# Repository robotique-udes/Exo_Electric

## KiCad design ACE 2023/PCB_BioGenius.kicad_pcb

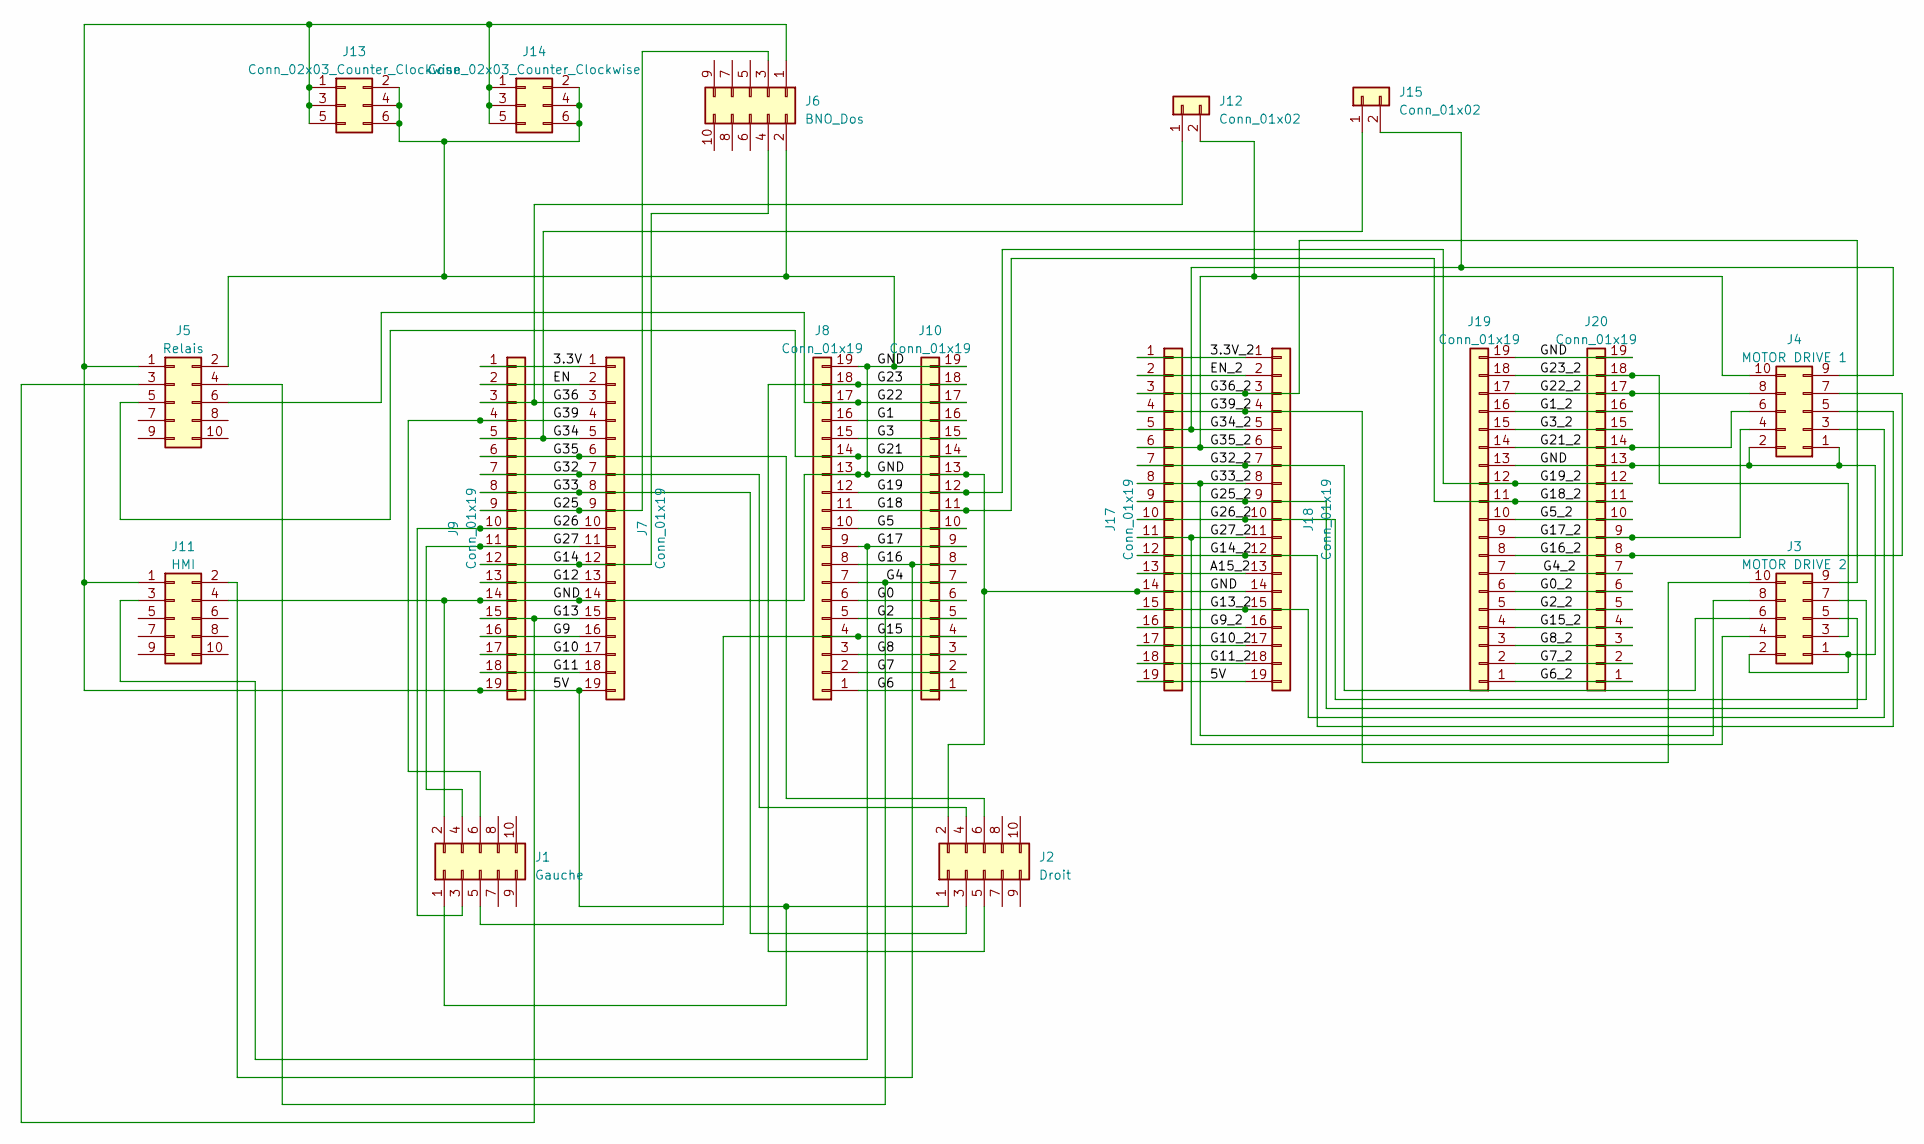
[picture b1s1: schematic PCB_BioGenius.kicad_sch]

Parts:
J1: Gauche; IDC-Header_2x05_P2.54mm_Vertical
J2: Droit; IDC-Header_2x05_P2.54mm_Vertical
J3: MOTOR DRIVE 2; IDC-Header_2x05_P2.54mm_Vertical
J4: MOTOR DRIVE 1; IDC-Header_2x05_P2.54mm_Vertical
J5: Relais; IDC-Header_2x05_P2.54mm_Vertical
J6: BNO_Dos; IDC-Header_2x05_P2.54mm_Vertical
J7, J8, J9, J10, J17, J18, J19, J20: Conn_01x19; PinSocket_1x19_P2.54mm_Vertical
J11: HMI; IDC-Header_2x05_P2.54mm_Vertical
J12, J15: Conn_01x02; PinHeader_1x02_P2.54mm_Vertical
J13, J14: Conn_02x03_Counter_Clockwise; PinSocket_2x03_P2.54mm_Vertical

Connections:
/3.3V: J7.1, J9.1
/3.3V_2: J17.1, J18.1
/A15_2: J17.13, J18.13
/EN: J7.2, J9.2
/EN_2: J17.2, J18.2
/G0: J8.6, J10.6
/G0_2: J19.6, J20.6
/G1: J8.16, J10.16
/G1_2: J19.16, J20.16
/G2: J8.5, J10.5
/G2_2: J19.5, J20.5
/G3: J8.15, J10.15
/G3_2: J19.15, J20.15
/G4: J5.4, J8.7, J10.7
/G4_2: J19.7, J20.7
/G5: J8.10, J10.10
/G5_2: J19.10, J20.10
/G6: J8.1, J10.1
/G6_2: J19.1, J20.1
/G7: J8.2, J10.2
/G7_2: J19.2, J20.2
/G8: J8.3, J10.3
/G8_2: J19.3, J20.3
/G9: J7.16, J9.16
/G9_2: J17.16, J18.16
/G10: J7.17, J9.17
/G10_2: J17.17, J18.17
/G11: J7.18, J9.18
/G11_2: J17.18, J18.18
/G12: J7.13, J9.13
/G13: J5.3, J7.15, J9.15
/G13_2: J4.3, J17.15, J18.15
/G14: J6.4, J7.12, J9.12
/G14_2: J4.5, J17.12, J18.12
/G15: J1.5, J8.4, J10.4
/G15_2: J19.4, J20.4
/G16: J8.8, J10.8, J11.2
/G16_2: J4.7, J19.8, J20.8
/G17: J8.9, J10.9, J11.3
/G17_2: J4.4, J19.9, J20.9
/G18: J8.11, J10.11, J19.11, J20.11
/G19: J8.12, J10.12, J19.12, J20.12
/G21: J5.5, J8.14, J10.14
/G21_2: J4.6, J19.14, J20.14
/G22: J5.6, J8.17, J10.17
/G22_2: J4.8, J19.17, J20.17
/G23: J2.5, J8.18, J10.18
/G23_2: J3.3, J19.18, J20.18
/G25: J6.3, J7.9, J9.9
/G25_2: J3.5, J17.9, J18.9
/G26: J1.3, J7.10, J9.10
/G26_2: J3.7, J17.10, J18.10
/G27: J1.4, J7.11, J9.11
/G27_2: J3.4, J17.11, J18.11
/G32: J2.4, J7.7, J9.7
/G32_2: J3.6, J17.7, J18.7
/G33: J2.3, J7.8, J9.8
/G33_2: J3.8, J17.8, J18.8
/G34: J7.5, J9.5, J15.1
/G34_2: J4.9, J15.2, J17.5, J18.5
/G35: J2.6, J7.6, J9.6
/G36_2: J3.9, J17.3, J18.3
/G39: J1.6, J7.4, J9.4
/G39_2: J3.10, J17.4, J18.4

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
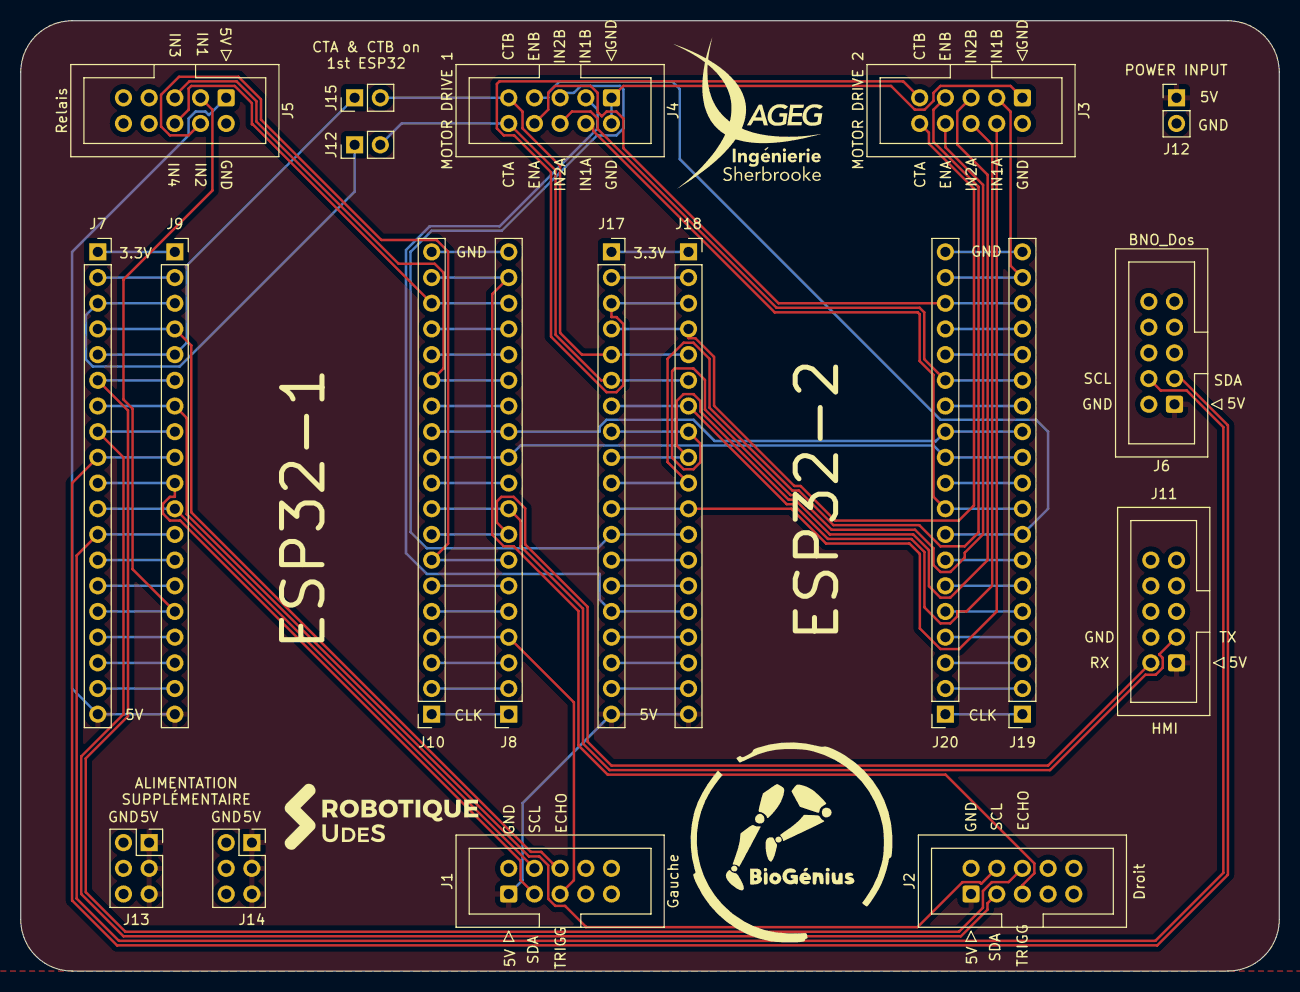
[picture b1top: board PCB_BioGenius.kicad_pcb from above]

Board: 2 copper layers, 124.5 x 94.0 mm, 20 parts (0 on the bottom side), 68 nets.

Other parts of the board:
J12#2: Conn_01x02; PinHeader_1x02_P2.54mm_Vertical

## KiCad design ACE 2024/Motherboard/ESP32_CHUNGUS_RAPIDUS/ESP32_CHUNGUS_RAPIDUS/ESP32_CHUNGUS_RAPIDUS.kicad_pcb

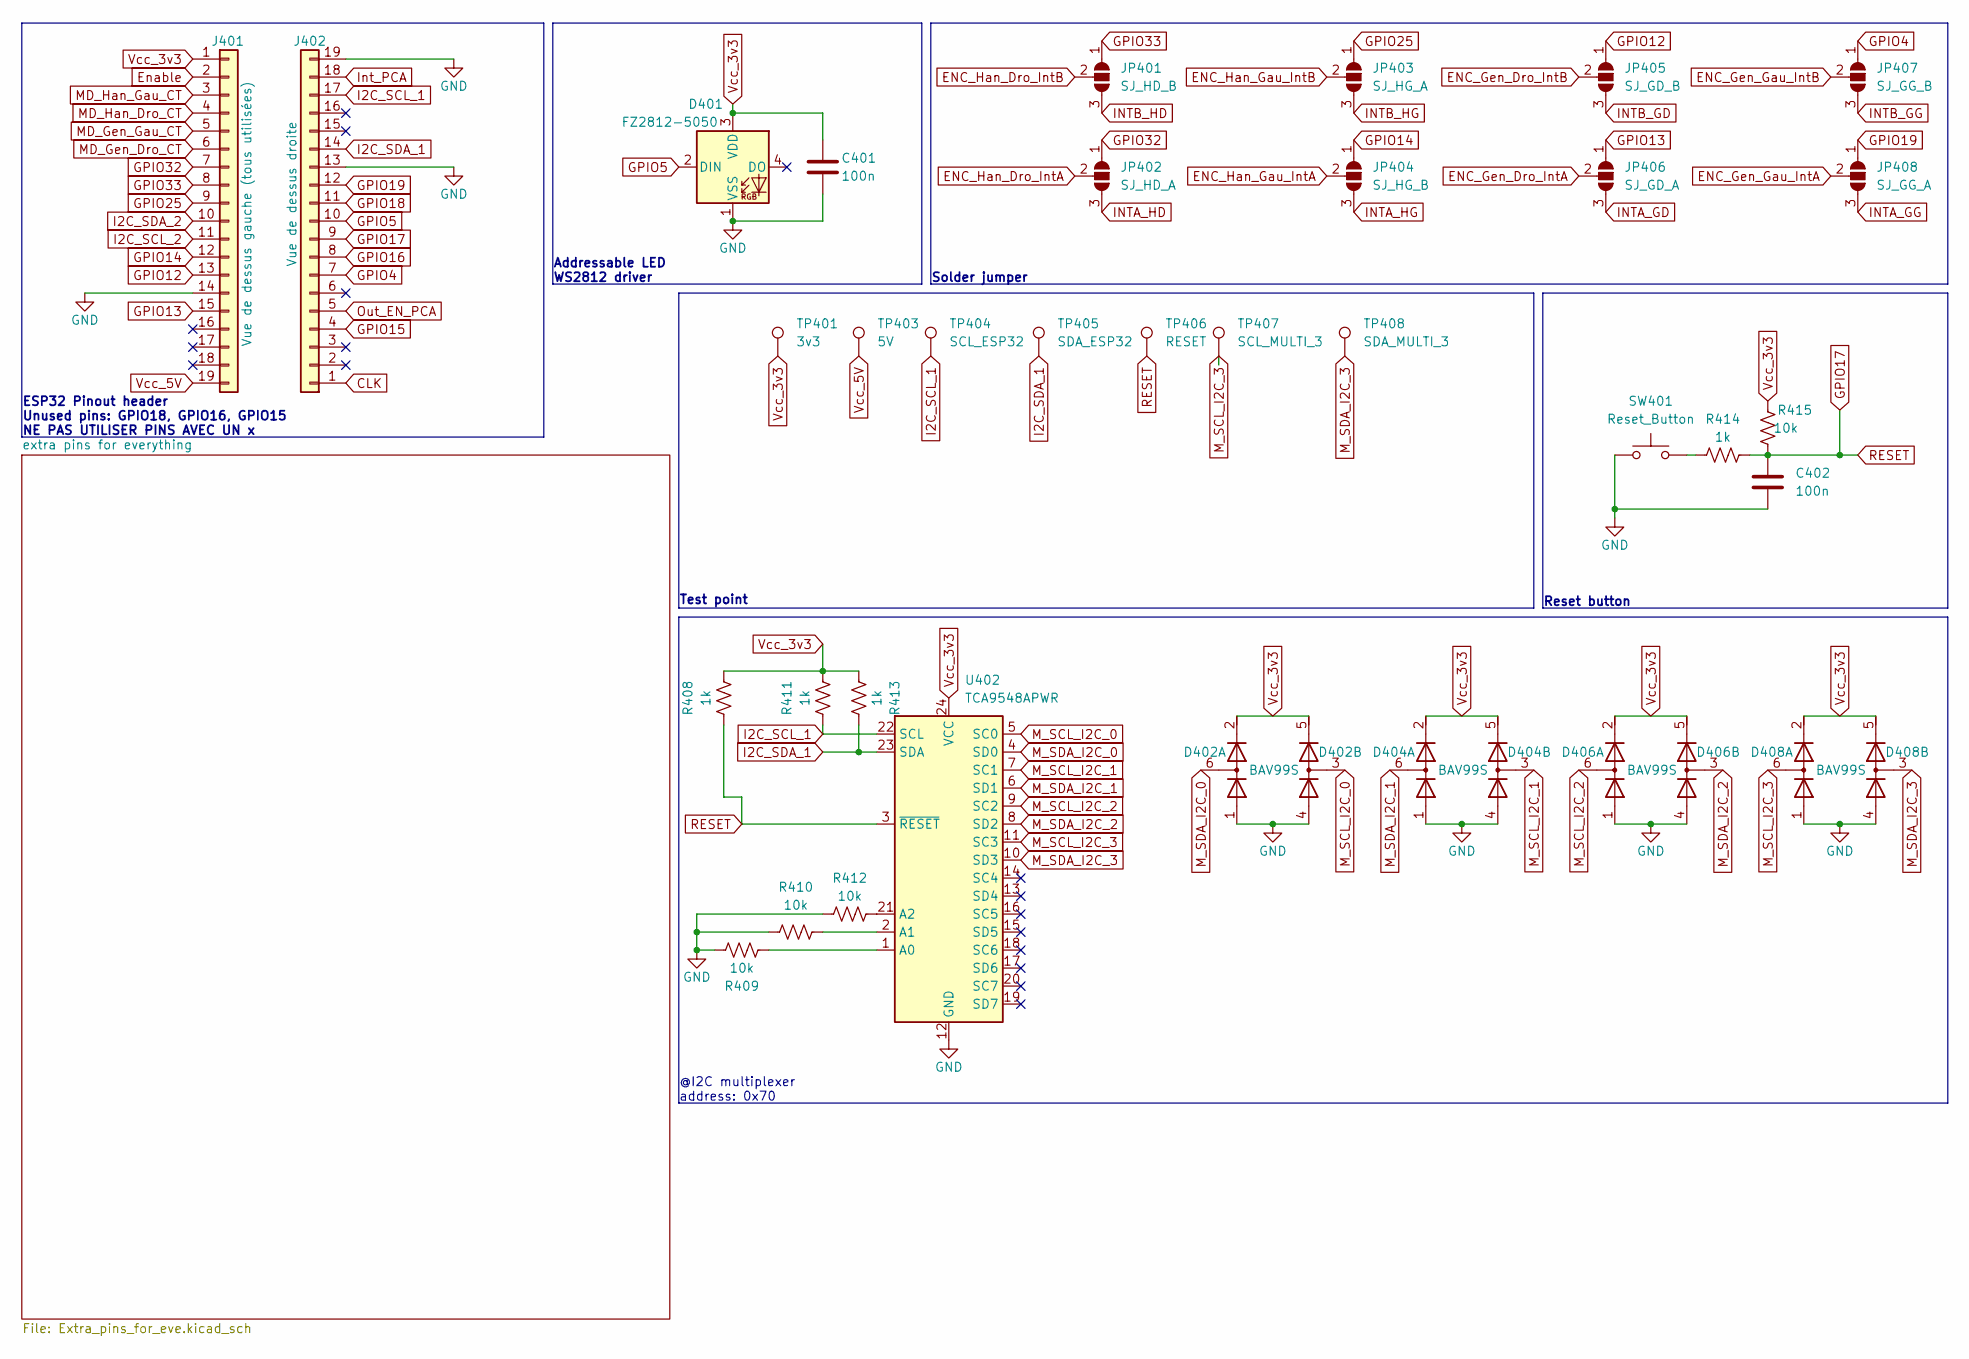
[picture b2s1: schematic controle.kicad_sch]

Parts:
C401, C402: 100n; C_0805_2012Metric
D401: FZ2812-5050; LED_Inolux_IN-PI554FCH_PLCC4_5.0x5.0mm_P3.2mm
D402, D404, D406, D408: BAV99S; SOT-363_SC-70-6
J401: Vue de dessus gauche (tous utilisées); PinSocket_1x19_P2.54mm_Vertical
J402: Vue de dessus droite; PinSocket_1x19_P2.54mm_Vertical
JP401: SJ_HD_B; SolderJumper-3_P2.0mm_Open_TrianglePad1.0x1.5mm_NumberLabels
JP402: SJ_HD_A; SolderJumper-3_P2.0mm_Open_TrianglePad1.0x1.5mm_NumberLabels
JP403: SJ_HG_A; SolderJumper-3_P2.0mm_Open_TrianglePad1.0x1.5mm_NumberLabels
JP404: SJ_HG_B; SolderJumper-3_P2.0mm_Open_TrianglePad1.0x1.5mm_NumberLabels
JP405: SJ_GD_B; SolderJumper-3_P2.0mm_Open_TrianglePad1.0x1.5mm_NumberLabels
JP406: SJ_GD_A; SolderJumper-3_P2.0mm_Open_TrianglePad1.0x1.5mm_NumberLabels
JP407: SJ_GG_B; SolderJumper-3_P2.0mm_Open_TrianglePad1.0x1.5mm_NumberLabels
JP408: SJ_GG_A; SolderJumper-3_P2.0mm_Open_TrianglePad1.0x1.5mm_NumberLabels
R408, R411, R413, R414: 1k; R_0805_2012Metric
R409, R410, R412, R415: 10k; R_0805_2012Metric
SW401: Reset_Button; SW_SPST_PTS645
TP401: 3v3; TestPoint_THTPad_2.5x2.5mm_Drill1.2mm
TP403: 5V; TestPoint_THTPad_2.5x2.5mm_Drill1.2mm
TP404: SCL_ESP32; TestPoint_THTPad_2.5x2.5mm_Drill1.2mm
TP405: SDA_ESP32; TestPoint_THTPad_2.5x2.5mm_Drill1.2mm
TP406: RESET; TestPoint_THTPad_2.5x2.5mm_Drill1.2mm
TP407: SCL_MULTI_3; TestPoint_THTPad_2.5x2.5mm_Drill1.2mm
TP408: SDA_MULTI_3; TestPoint_THTPad_2.5x2.5mm_Drill1.2mm
U402: TCA9548APWR; TSSOP-24_4.4x7.8mm_P0.65mm

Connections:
CLK: J402.1
ENC_Gen_Dro_IntA: JP406.2 (C); also elsewhere on the board
ENC_Gen_Dro_IntB: JP405.2 (C); also elsewhere on the board
ENC_Gen_Gau_IntA: JP408.2 (C); also elsewhere on the board
ENC_Gen_Gau_IntB: JP407.2 (C); also elsewhere on the board
ENC_Han_Dro_IntA: JP402.2 (C); also elsewhere on the board
ENC_Han_Dro_IntB: JP401.2 (C); also elsewhere on the board
ENC_Han_Gau_IntA: JP404.2 (C); also elsewhere on the board
ENC_Han_Gau_IntB: JP403.2 (C); also elsewhere on the board
Enable: J401.2
GND: C401.2, C402.2, D401.1 (VSS), D402.1 (A1), D402.4 (A3), D404.1 (A1), D404.4 (A3), D406.1 (A1), D406.4 (A3), D408.1 (A1), D408.4 (A3), J401.14, J402.13, J402.19, R409.1, R410.2, R412.2, SW401.1, U402.12 (GND); also elsewhere on the board
GPIO4: J402.7, JP407.1 (A)
GPIO5: D401.2 (DIN), J402.10
GPIO12: J401.13, JP405.1 (A)
GPIO13: J401.15, JP406.1 (A)
GPIO14: J401.12, JP404.1 (A)
GPIO15: J402.4
GPIO16: J402.8
GPIO17: C402.1, J402.9, R408.2, R414.1, R415.2, TP406.1, U402.3 (~RESET); also elsewhere on the board
GPIO18: J402.11
GPIO19: J402.12, JP408.1 (A)
GPIO25: J401.9, JP403.1 (A)
GPIO32: J401.7, JP402.1 (A)
GPIO33: J401.8, JP401.1 (A)
I2C_SCL_1: J402.17, R411.2, TP404.1, U402.22 (SCL); also elsewhere on the board
I2C_SCL_2: J401.11
I2C_SDA_1: J402.14, R413.1, TP405.1, U402.23 (SDA); also elsewhere on the board
I2C_SDA_2: J401.10
INTA_GD: JP406.3 (B); also elsewhere on the board
INTA_GG: JP408.3 (B); also elsewhere on the board
INTA_HD: JP402.3 (B); also elsewhere on the board
INTA_HG: JP404.3 (B); also elsewhere on the board
INTB_GD: JP405.3 (B); also elsewhere on the board
INTB_GG: JP407.3 (B); also elsewhere on the board
INTB_HD: JP401.3 (B); also elsewhere on the board
INTB_HG: JP403.3 (B); also elsewhere on the board
Int_PCA: J402.18; also elsewhere on the board
MD_Gen_Dro_CT: J401.6; also elsewhere on the board
MD_Gen_Gau_CT: J401.5; also elsewhere on the board
MD_Han_Dro_CT: J401.4; also elsewhere on the board
MD_Han_Gau_CT: J401.3; also elsewhere on the board
M_SCL_I2C_0: D402.3 (K1A2), U402.5 (SC0); also elsewhere on the board
M_SCL_I2C_1: D404.3 (K1A2), U402.7 (SC1); also elsewhere on the board
M_SCL_I2C_2: D406.6 (K3A4), U402.9 (SC2); also elsewhere on the board
M_SCL_I2C_3: D408.6 (K3A4), TP407.1, U402.11 (SC3)
M_SDA_I2C_0: D402.6 (K3A4), U402.4 (SD0); also elsewhere on the board
M_SDA_I2C_1: D404.6 (K3A4), U402.6 (SD1); also elsewhere on the board
M_SDA_I2C_2: D406.3 (K1A2), U402.8 (SD2); also elsewhere on the board
M_SDA_I2C_3: D408.3 (K1A2), TP408.1, U402.10 (SD3)
unnamed: R414.2, SW401.2
unnamed: R409.2, U402.1 (A0)
unnamed: R410.1, U402.2 (A1)
unnamed: R412.1, U402.21 (A2)
Out_EN_PCA: J402.5; also elsewhere on the board
Vcc_3v3: C401.1, D401.3 (VDD), D402.2 (K2), D402.5 (K4), D404.2 (K2), D404.5 (K4), D406.2 (K2), D406.5 (K4), D408.2 (K2), D408.5 (K4), J401.1, R408.1, R411.1, R413.2, R415.1, TP401.1, U402.24 (VCC); also elsewhere on the board
Vcc_5V: J401.19, TP403.1; also elsewhere on the board

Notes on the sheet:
Reset button
@I2C multiplexer address: 0x70
ESP32 Pinout header Unused pins: GPIO18, GPIO16, GPIO15 NE PAS UTILISER PINS AVEC UN x
Solder jumper
Addressable LED WS2812 driver
Test point

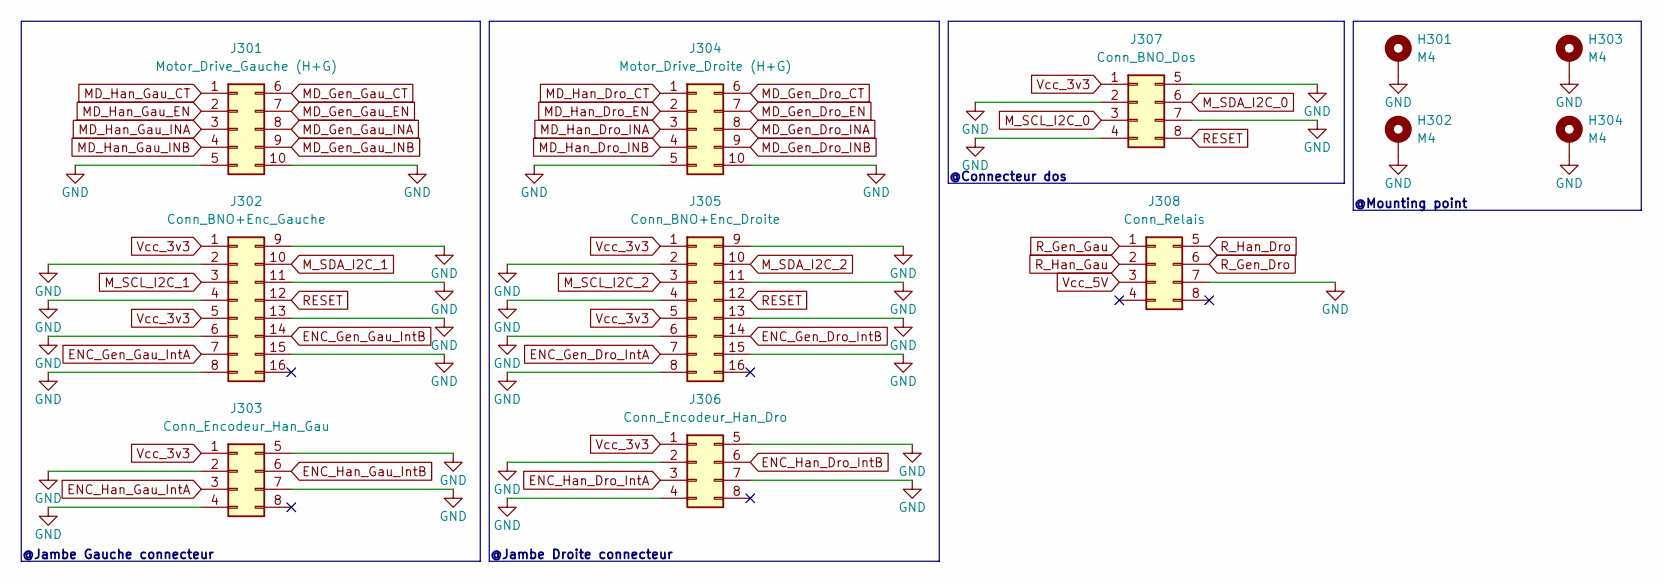
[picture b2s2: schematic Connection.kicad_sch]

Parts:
H301, H302, H303, H304: M4; MountingHole_4.3mm_M4_ISO7380_Pad
J301: Motor_Drive_Gauche (H+G); Molex_Nano-Fit_105310-xx10_2x05_P2.50mm_Vertical
J302: Conn_BNO+Enc_Gauche; Molex_Nano-Fit_105310-xx16_2x08_P2.50mm_Vertical
J303: Conn_Encodeur_Han_Gau; Molex_Nano-Fit_105310-xx08_2x04_P2.50mm_Vertical
J304: Motor_Drive_Droite (H+G); Molex_Nano-Fit_105310-xx10_2x05_P2.50mm_Vertical
J305: Conn_BNO+Enc_Droite; Molex_Nano-Fit_105310-xx16_2x08_P2.50mm_Vertical
J306: Conn_Encodeur_Han_Dro; Molex_Nano-Fit_105310-xx08_2x04_P2.50mm_Vertical
J307: Conn_BNO_Dos; Molex_Nano-Fit_105310-xx08_2x04_P2.50mm_Vertical
J308: Conn_Relais; Molex_Nano-Fit_105310-xx08_2x04_P2.50mm_Vertical

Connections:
ENC_Gen_Dro_IntA: J305.7; also elsewhere on the board
ENC_Gen_Dro_IntB: J305.14; also elsewhere on the board
ENC_Gen_Gau_IntA: J302.7; also elsewhere on the board
ENC_Gen_Gau_IntB: J302.14; also elsewhere on the board
ENC_Han_Dro_IntA: J306.3; also elsewhere on the board
ENC_Han_Dro_IntB: J306.6; also elsewhere on the board
ENC_Han_Gau_IntA: J303.3; also elsewhere on the board
ENC_Han_Gau_IntB: J303.6; also elsewhere on the board
GND: H301.1, H302.1, H303.1, H304.1, J301.5, J301.10, J302.2, J302.4, J302.6, J302.8, J302.9, J302.11, J302.13, J302.15, J303.2, J303.4, J303.5, J303.7, J304.5, J304.10, J305.2, J305.4, J305.6, J305.8, J305.9, J305.11, J305.13, J305.15, J306.2, J306.4, J306.5, J306.7, J307.2, J307.4, J307.5, J307.7, J308.7; also elsewhere on the board
GPIO17: J302.12, J305.12, J307.8; also elsewhere on the board
MD_Gen_Dro_CT: J304.6; also elsewhere on the board
MD_Gen_Dro_EN: J304.7; also elsewhere on the board
MD_Gen_Dro_INA: J304.8; also elsewhere on the board
MD_Gen_Dro_INB: J304.9; also elsewhere on the board
MD_Gen_Gau_CT: J301.6; also elsewhere on the board
MD_Gen_Gau_EN: J301.7; also elsewhere on the board
MD_Gen_Gau_INA: J301.8; also elsewhere on the board
MD_Gen_Gau_INB: J301.9; also elsewhere on the board
MD_Han_Dro_CT: J304.1; also elsewhere on the board
MD_Han_Dro_EN: J304.2; also elsewhere on the board
MD_Han_Dro_INA: J304.3; also elsewhere on the board
MD_Han_Dro_INB: J304.4; also elsewhere on the board
MD_Han_Gau_CT: J301.1; also elsewhere on the board
MD_Han_Gau_EN: J301.2; also elsewhere on the board
MD_Han_Gau_INA: J301.3; also elsewhere on the board
MD_Han_Gau_INB: J301.4; also elsewhere on the board
M_SCL_I2C_0: J307.3; also elsewhere on the board
M_SCL_I2C_1: J302.3; also elsewhere on the board
M_SCL_I2C_2: J305.3; also elsewhere on the board
M_SDA_I2C_0: J307.6; also elsewhere on the board
M_SDA_I2C_1: J302.10; also elsewhere on the board
M_SDA_I2C_2: J305.10; also elsewhere on the board
R_Gen_Dro: J308.6; also elsewhere on the board
R_Gen_Gau: J308.1; also elsewhere on the board
R_Han_Dro: J308.5; also elsewhere on the board
R_Han_Gau: J308.2; also elsewhere on the board
Vcc_3v3: J302.1, J302.5, J303.1, J305.1, J305.5, J306.1, J307.1; also elsewhere on the board
Vcc_5V: J308.3; also elsewhere on the board

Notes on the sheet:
@Jambe Gauche connecteur
@Mounting point
@Jambe Droite connecteur
@Connecteur dos

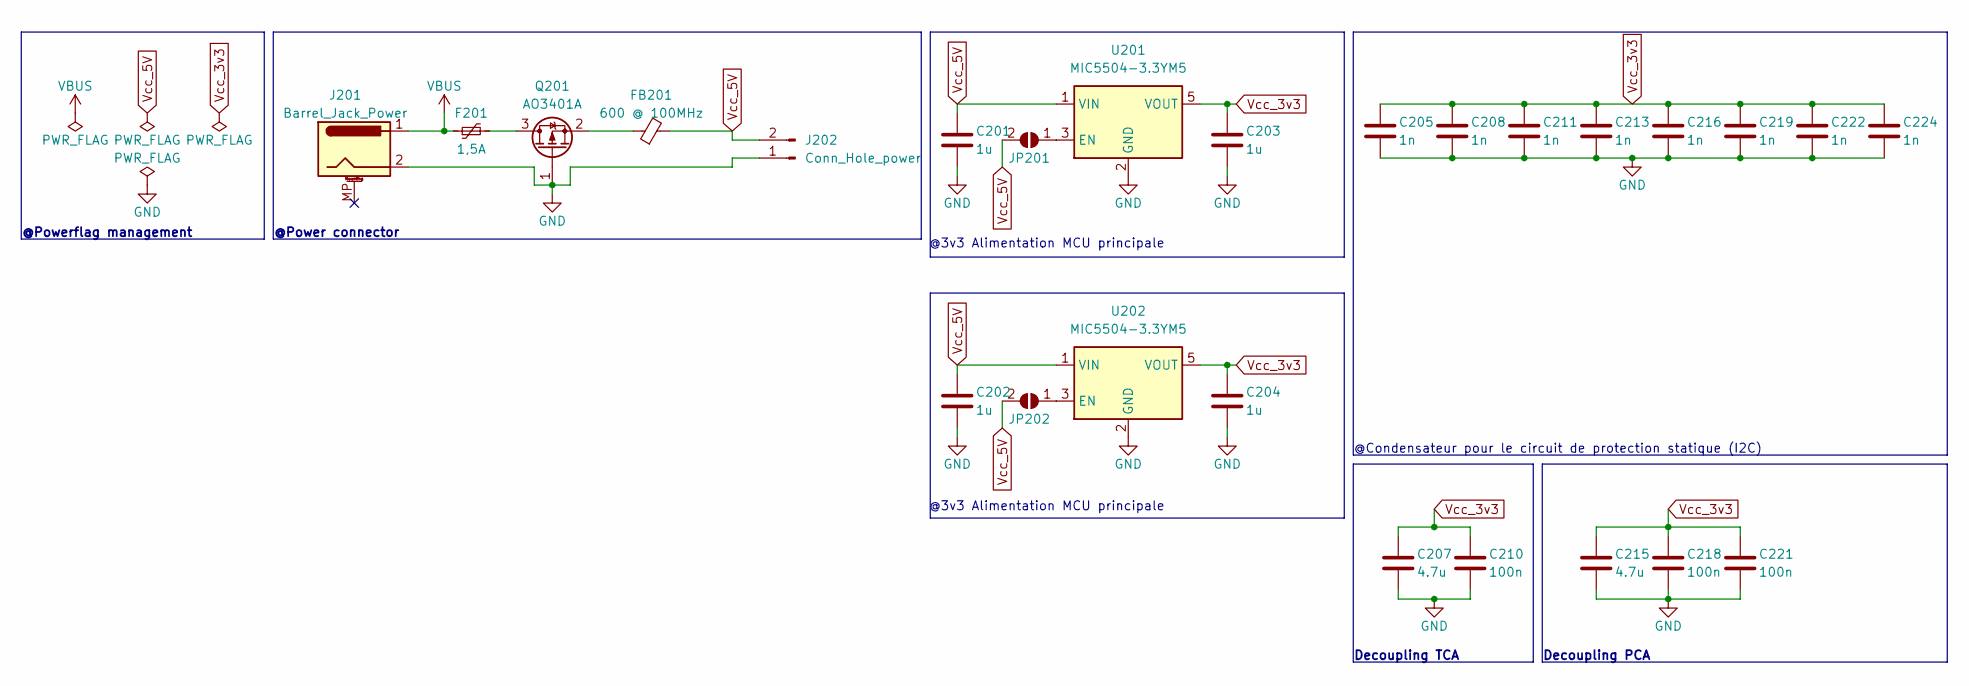
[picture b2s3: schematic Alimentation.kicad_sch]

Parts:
C201, C202, C203, C204: 1u; C_0805_2012Metric
C205, C208, C211, C213, C216, C219, C222, C224: 1n; C_1206_3216Metric
C207, C215: 4.7u; C_0805_2012Metric
C210, C218, C221: 100n; C_0805_2012Metric
F201: 1,5A; Fuse_1812_4532Metric_Pad1.30x3.40mm_HandSolder
FB201: 600 @ 100MHz; R_0805_2012Metric_Pad1.20x1.40mm_HandSolder
J201: Barrel_Jack_Power; BarrelJack_Horizontal
J202: Conn_Hole_power; SolderWire-1.5sqmm_1x02_P7.8mm_D1.7mm_OD3.9mm
JP201, JP202: SolderJumper_2_Open; SolderJumper-2_P1.3mm_Open_TrianglePad1.0x1.5mm
Q201: AO3401A; SOT-23
U201, U202: MIC5504-3.3YM5; SOT-23-5

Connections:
GND: C201.2, C202.2, C203.2, C204.2, C205.2, C207.2, C208.2, C210.2, C211.2, C213.2, C215.2, C216.2, C218.2, C219.2, C221.2, C222.2, C224.2, J201.2, J202.1, Q201.1 (G), U201.2 (GND), U202.2 (GND); also elsewhere on the board
unnamed: JP201.1 (A), U201.3 (EN)
unnamed: JP202.1 (A), U202.3 (EN)
unnamed: F201.2, Q201.3 (D)
unnamed: FB201.1, Q201.2 (S)
VBUS: F201.1, J201.1
Vcc_3v3: C203.1, C204.1, C205.1, C207.1, C208.1, C210.1, C211.1, C213.1, C215.1, C216.1, C218.1, C219.1, C221.1, C222.1, C224.1, U201.5 (VOUT), U202.5 (VOUT); also elsewhere on the board
Vcc_5V: C201.1, C202.1, FB201.2, J202.2, JP201.2 (B), JP202.2 (B), U201.1 (VIN), U202.1 (VIN); also elsewhere on the board

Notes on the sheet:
@Powerflag management
Decoupling PCA
@Power connector
Decoupling TCA
@3v3 Alimentation MCU principale
@Condensateur pour le circuit de protection statique (I2C)

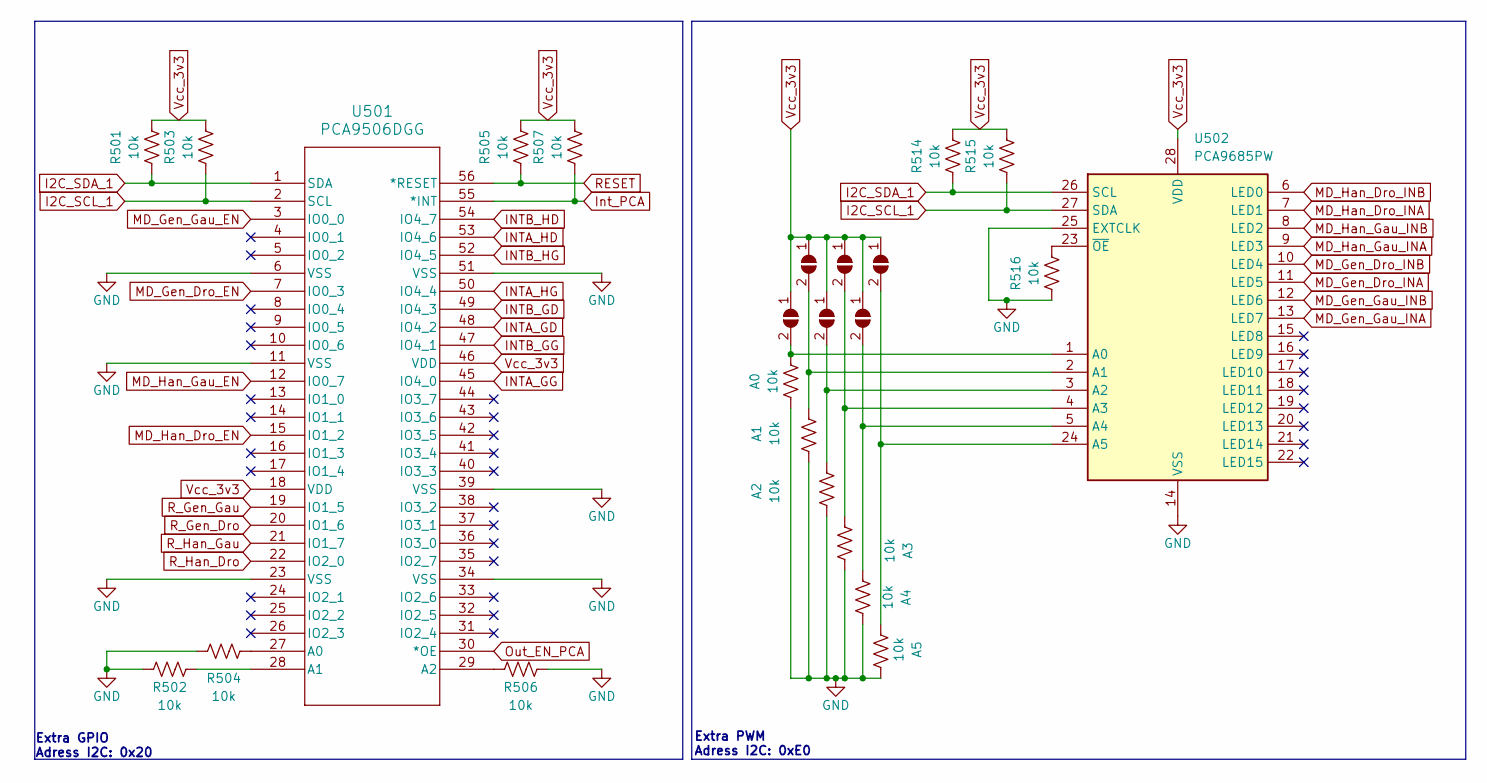
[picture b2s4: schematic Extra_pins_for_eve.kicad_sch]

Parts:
A0, A1, A2, A3, A4, A5: 10k; R_0805_2012Metric
JP501, JP502, JP505, JP506, JP507, JP508: SolderJumper_2_Open; SolderJumper-2_P1.3mm_Open_TrianglePad1.0x1.5mm
R501, R502, R503, R504, R505, R506, R507, R514, R515, R516: 10k; R_0805_2012Metric
U501: PCA9506DGG; TSSOP-56_6.1x14mm_P0.5mm
U502: PCA9685PW; TSSOP-28_4.4x9.7mm_P0.65mm

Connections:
GND: A0.1, A1.1, A2.1, A3.1, A4.1, A5.1, R502.2, R504.2, R506.1, R516.1, U501.6 (VSS), U501.11 (VSS), U501.23 (VSS), U501.34 (VSS), U501.39 (VSS), U501.51 (VSS), U502.14 (VSS), U502.25 (EXTCLK); also elsewhere on the board
GPIO17: R505.1, U501.56 (*RESET); also elsewhere on the board
I2C_SCL_1: R503.1, R515.1, U501.2 (SCL), U502.27 (SDA); also elsewhere on the board
I2C_SDA_1: R501.1, R514.1, U501.1 (SDA), U502.26 (SCL); also elsewhere on the board
INTA_GD: U501.48 (IO4_2); also elsewhere on the board
INTA_GG: U501.45 (IO4_0); also elsewhere on the board
INTA_HD: U501.53 (IO4_6); also elsewhere on the board
INTA_HG: U501.50 (IO4_4); also elsewhere on the board
INTB_GD: U501.49 (IO4_3); also elsewhere on the board
INTB_GG: U501.47 (IO4_1); also elsewhere on the board
INTB_HD: U501.54 (IO4_7); also elsewhere on the board
INTB_HG: U501.52 (IO4_5); also elsewhere on the board
Int_PCA: R507.1, U501.55 (*INT); also elsewhere on the board
MD_Gen_Dro_EN: U501.7 (IO0_3); also elsewhere on the board
MD_Gen_Dro_INA: U502.11 (LED5); also elsewhere on the board
MD_Gen_Dro_INB: U502.10 (LED4); also elsewhere on the board
MD_Gen_Gau_EN: U501.3 (IO0_0); also elsewhere on the board
MD_Gen_Gau_INA: U502.13 (LED7); also elsewhere on the board
MD_Gen_Gau_INB: U502.12 (LED6); also elsewhere on the board
MD_Han_Dro_EN: U501.15 (IO1_2); also elsewhere on the board
MD_Han_Dro_INA: U502.7 (LED1); also elsewhere on the board
MD_Han_Dro_INB: U502.6 (LED0); also elsewhere on the board
MD_Han_Gau_EN: U501.12 (IO0_7); also elsewhere on the board
MD_Han_Gau_INA: U502.9 (LED3); also elsewhere on the board
MD_Han_Gau_INB: U502.8 (LED2); also elsewhere on the board
unnamed: A0.2, JP501.2 (B), U502.1 (A0)
unnamed: A1.2, JP502.2 (B), U502.2 (A1)
unnamed: A2.2, JP505.2 (B), U502.3 (A2)
unnamed: A3.2, JP506.2 (B), U502.4 (A3)
unnamed: A4.2, JP507.2 (B), U502.5 (A4)
unnamed: A5.2, JP508.2 (B), U502.24 (A5)
unnamed: R504.1, U501.27 (A0)
unnamed: R502.1, U501.28 (A1)
unnamed: R506.2, U501.29 (A2)
unnamed: R516.2, U502.23 (~OE)
Out_EN_PCA: U501.30 (*OE); also elsewhere on the board
R_Gen_Dro: U501.20 (IO1_6); also elsewhere on the board
R_Gen_Gau: U501.19 (IO1_5); also elsewhere on the board
R_Han_Dro: U501.22 (IO2_0); also elsewhere on the board
R_Han_Gau: U501.21 (IO1_7); also elsewhere on the board
Vcc_3v3: JP501.1 (A), JP502.1 (A), JP505.1 (A), JP506.1 (A), JP507.1 (A), JP508.1 (A), R501.2, R503.2, R505.2, R507.2, R514.2, R515.2, U501.18 (VDD), U501.46 (VDD), U502.28 (VDD); also elsewhere on the board

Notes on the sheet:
Extra PWM Adress I2C: 0xE0
Extra GPIO Adress I2C: 0x20

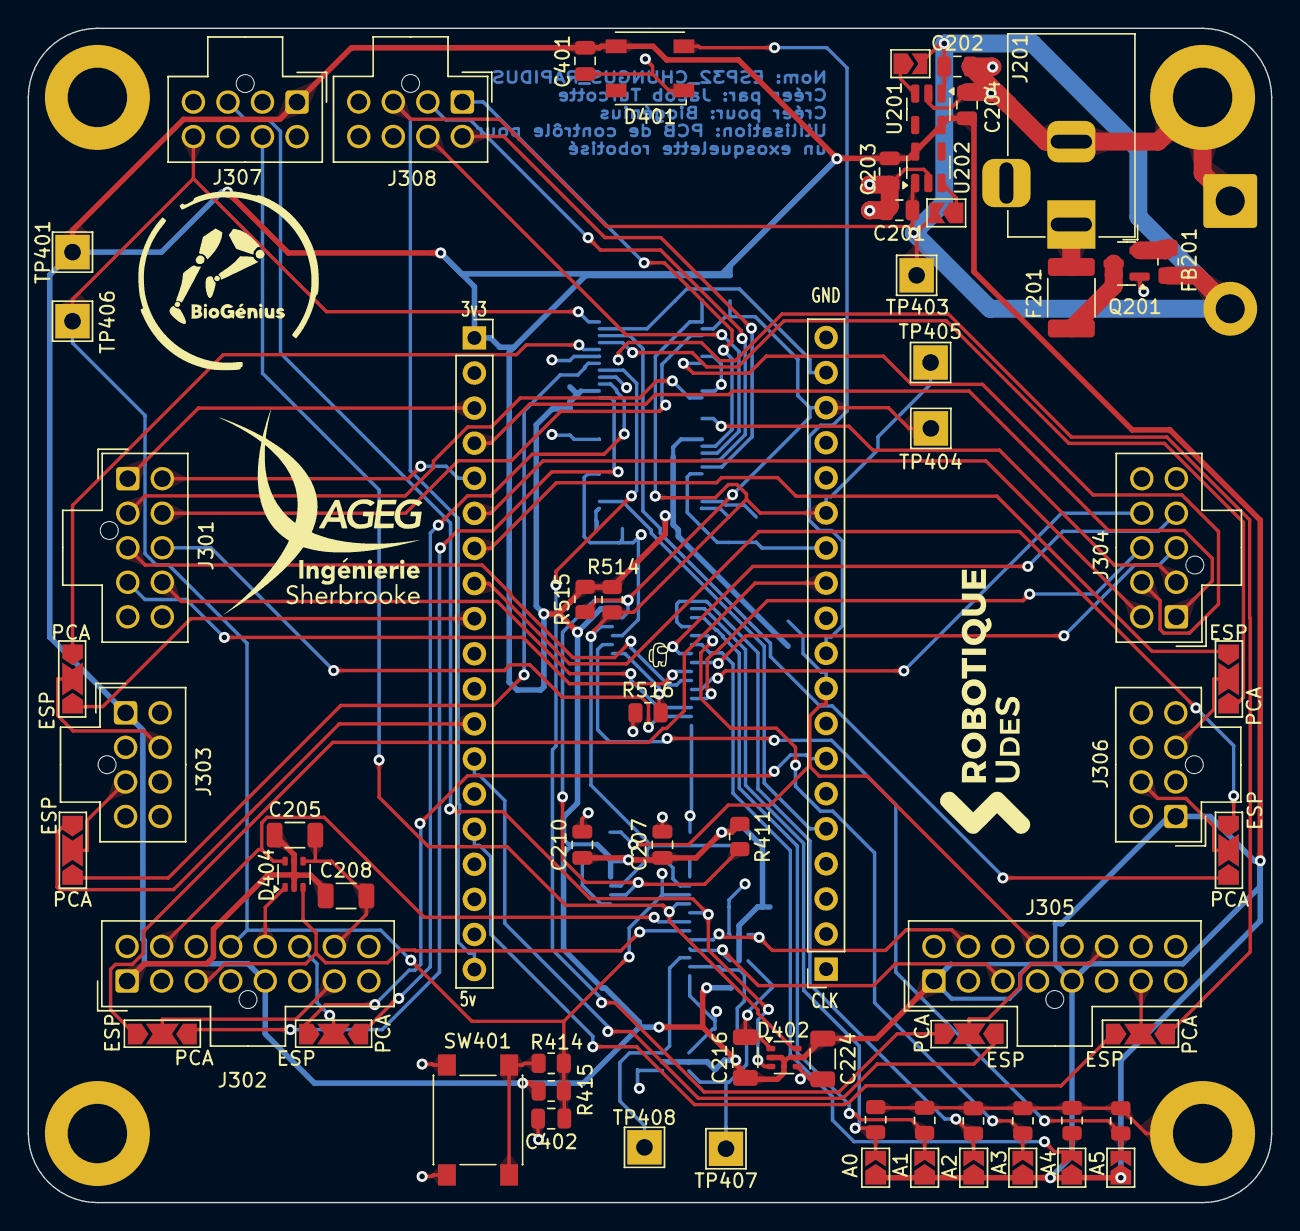
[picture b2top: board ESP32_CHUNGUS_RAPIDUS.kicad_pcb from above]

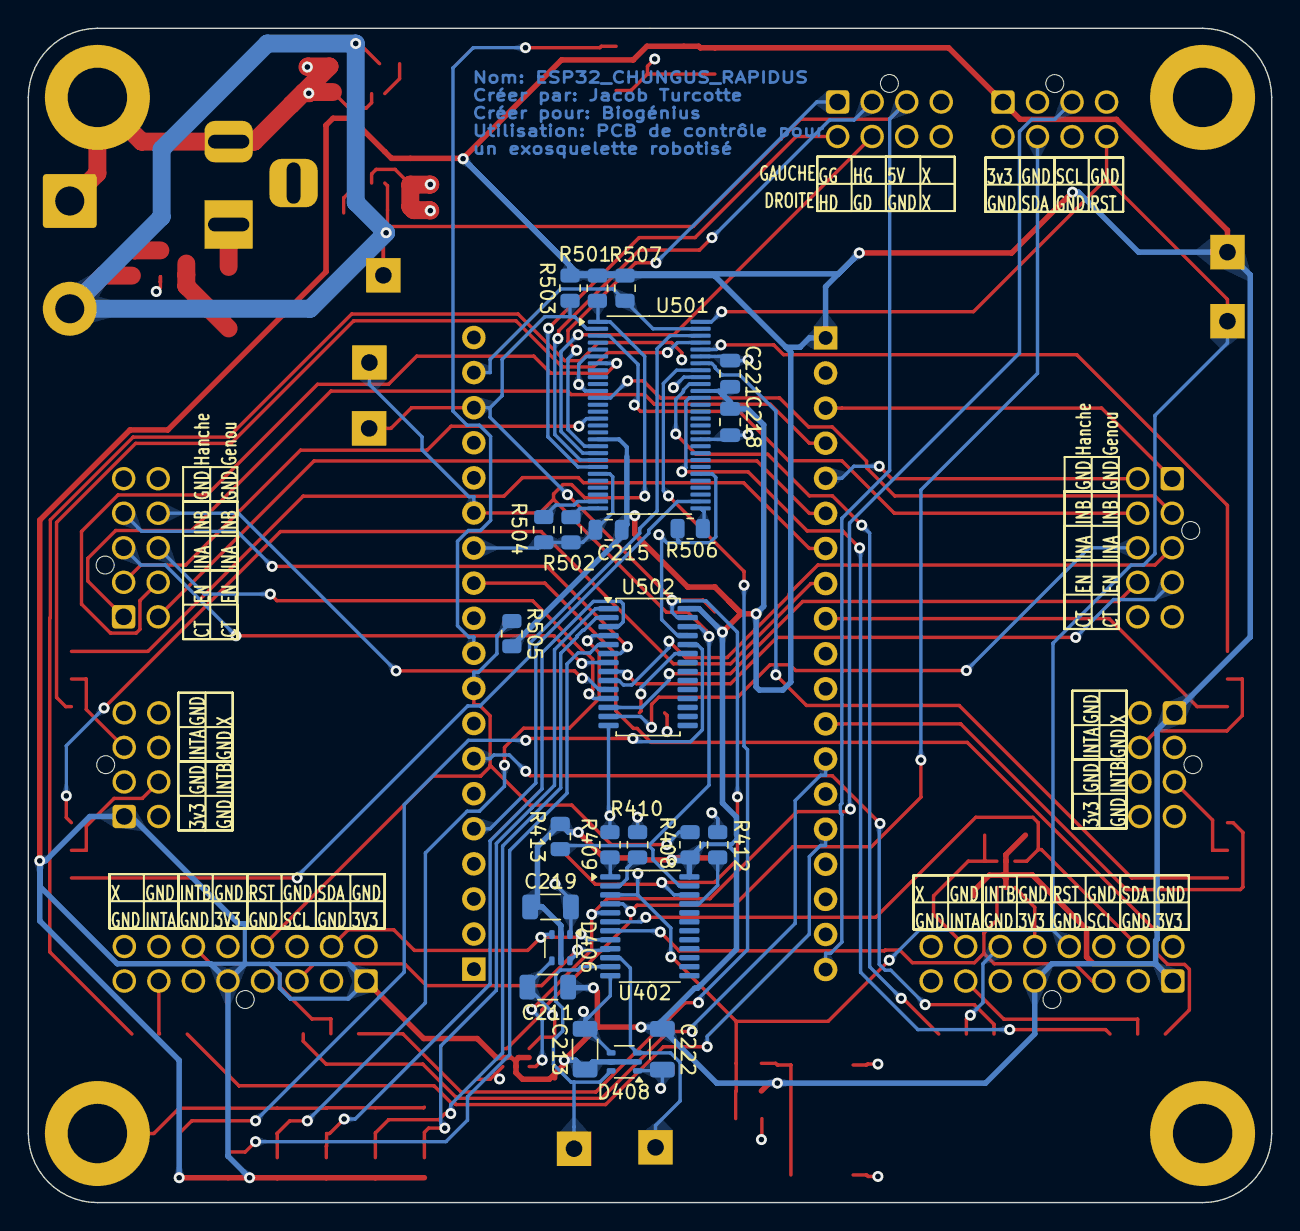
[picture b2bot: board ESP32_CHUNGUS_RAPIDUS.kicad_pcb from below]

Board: 4 copper layers, 90.0 x 85.0 mm, 96 parts (24 on the bottom side), 80 nets.

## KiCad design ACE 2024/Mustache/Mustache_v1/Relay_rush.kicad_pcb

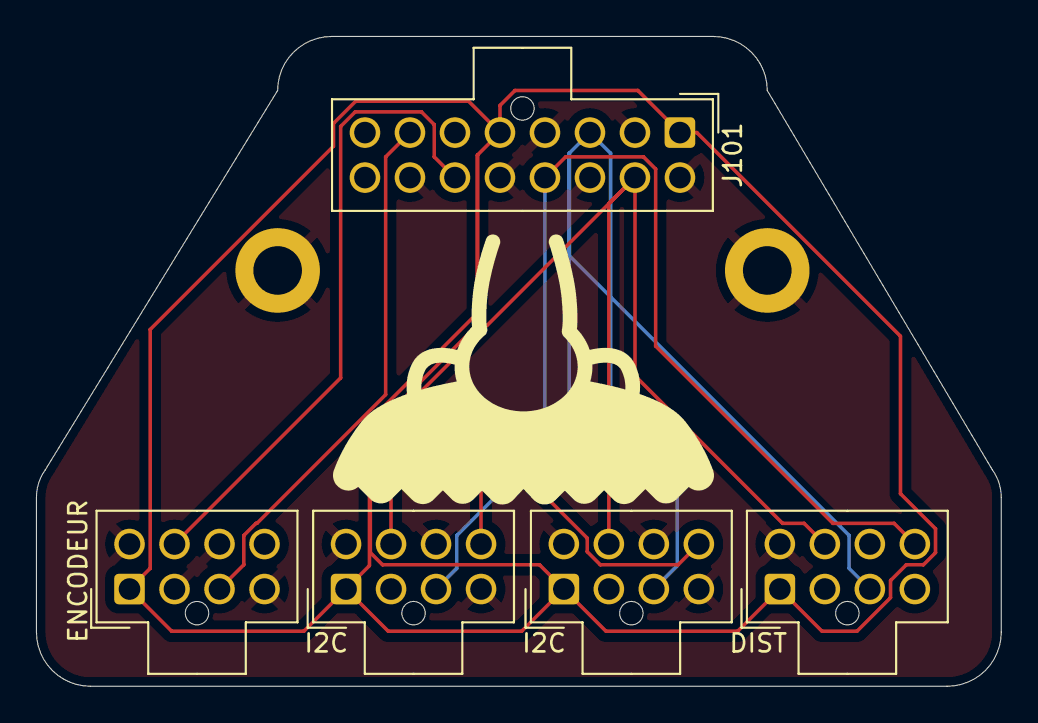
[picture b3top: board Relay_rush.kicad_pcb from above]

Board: 2 copper layers, 53.6 x 36.1 mm, 5 parts (0 on the bottom side), 7 nets.

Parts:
DIST: Conn_Capt_Distance; Molex_Nano-Fit_105310-xx08_2x04_P2.50mm_Vertical
ENCODEUR: Conn_Encodeur; Molex_Nano-Fit_105310-xx08_2x04_P2.50mm_Vertical
I2C, I2C#2: Conn_I2C; Molex_Nano-Fit_105310-xx08_2x04_P2.50mm_Vertical
J101: Conn_I2C+Enc; Molex_Nano-Fit_105310-xx16_2x08_P2.50mm_Vertical

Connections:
ENC_IntA: ENCODEUR.3, J101.7
ENC_IntB: ENCODEUR.6, J101.14
GND: DIST.5, ENCODEUR.2, ENCODEUR.4, ENCODEUR.5, ENCODEUR.7, I2C.2, I2C.4, I2C.5, I2C.7, I2C#2.2, I2C#2.4, I2C#2.5, I2C#2.7, J101.2, J101.4, J101.6, J101.8, J101.9, J101.11, J101.13, J101.15
RESET: DIST.8, I2C.8, I2C#2.8, J101.12
SCL_I2C: DIST.3, I2C.3, I2C#2.3, J101.3
SDA_I2C: DIST.6, I2C.6, I2C#2.6, J101.10
Vcc_3v3: DIST.1, ENCODEUR.1, I2C.1, I2C#2.1, J101.1, J101.5
